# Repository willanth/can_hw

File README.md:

# can_hw
CANBus interface hardware PCB design

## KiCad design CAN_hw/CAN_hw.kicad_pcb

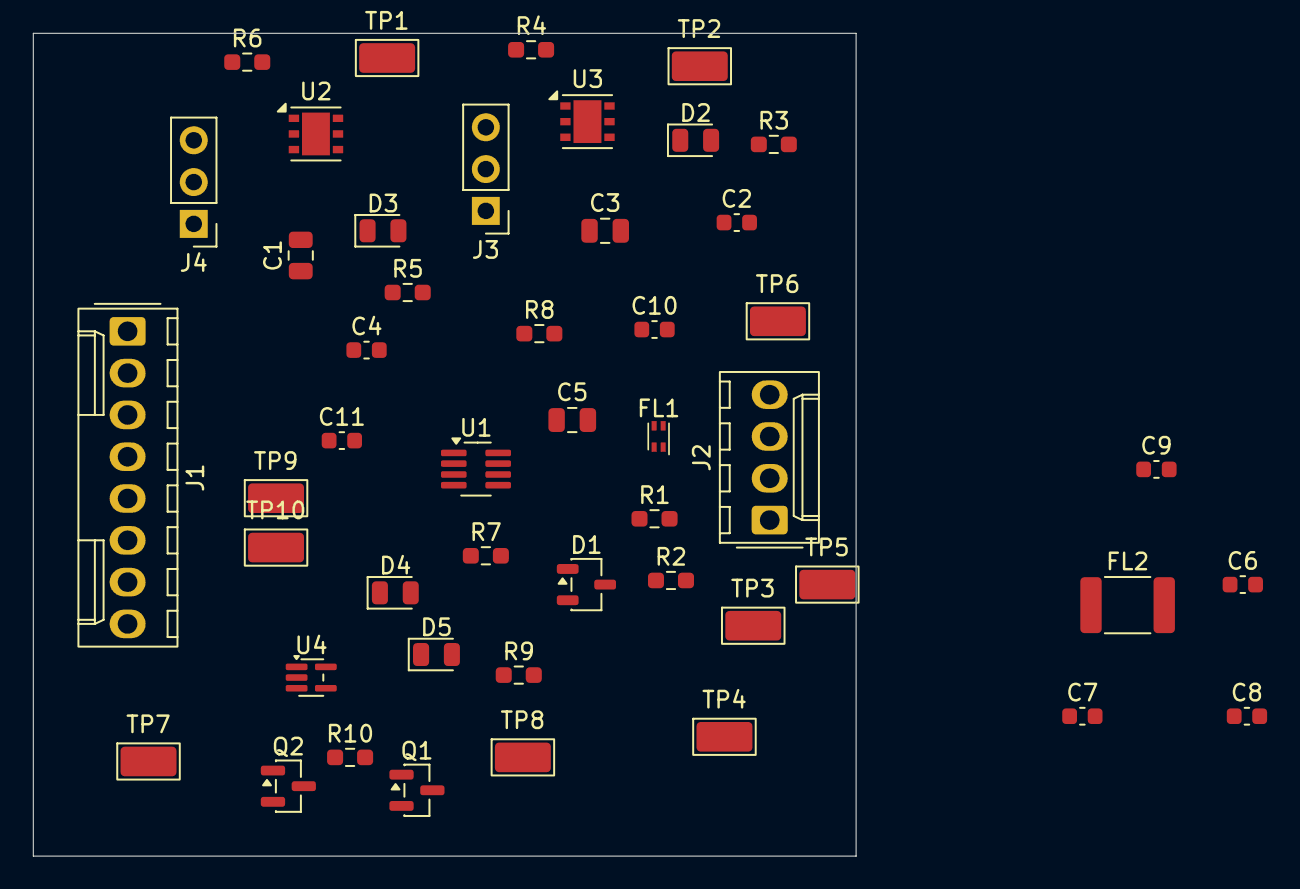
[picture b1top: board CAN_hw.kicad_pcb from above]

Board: 2 copper layers, 50.0 x 50.0 mm, 48 parts (0 on the bottom side), 26 nets, no tracks yet.

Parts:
C1: 4.7nF 50V; C_0805_2012Metric
C2, C4: 4.7uF 16V; C_0603_1608Metric
C3, C5: 4.7uF 50V; C_0805_2012Metric
C6, C7, C8, C9: 100pF; C_0603_1608Metric
C10, C11: 100nF; C_0603_1608Metric
D1: ESDA5V3L; SOT-23-3
D2, D3, D4, D5: LED; LED_0805_2012Metric
FL1: 0603USB-222; L_CommonModeChoke_Coilcraft_0603USB
FL2: ACT45-101; L_1812_4532Metric_Pad1.30x3.40mm_HandSolder
J1: Conn_01x08_Pin; Molex_KK-254_AE-6410-08A_1x08_P2.54mm_Vertical
J2: Conn_01x04_Pin; Molex_KK-254_AE-6410-04A_1x04_P2.54mm_Vertical
J3, J4: Conn_01x03_Pin; PinHeader_1x03_P2.54mm_Vertical
Q1, Q2: 2N7002; SOT-23
R1, R2: 60R; R_0603_1608Metric_Pad0.98x0.95mm_HandSolder
R3, R5, R9, R10: R; R_0603_1608Metric_Pad0.98x0.95mm_HandSolder
R4, R6, R7, R8: 10k; R_0603_1608Metric_Pad0.98x0.95mm_HandSolder
TP1, TP2, TP3, TP4, TP5, TP6, TP7, TP8, TP9, TP10: TestPoint_Alt; TestPoint_Keystone_5015_Micro_Mini
U1: TCAN337G; SOT-23-8_Handsoldering
U2: LDO40LPU50RY; DFN-6-1EP_3x3mm_P0.95mm_EP1.7x2.6mm
U3: LDO40LPU33RY; DFN-6-1EP_3x3mm_P0.95mm_EP1.7x2.6mm
U4: 74AHC1G04; SOT-353_SC-70-5

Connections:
+3.3V: C2.1, C10.1, C11.1, D2.2 (A), D4.2 (A), D5.2 (A), J1.3, R7.1, TP2.1, U1.3 (VCC), U3.4 (Vout), U3.5 (Vsense), U4.5 (VCC)
+5V: C4.1, D3.2 (A), J1.1, TP1.1, U2.4 (Vout), U2.5 (Vsense)
/CAN+: C9.2, D1.1 (K), J2.2, R1.1, TP3.1
/CAN-: C8.1, D1.2 (K), J2.3, R2.2, TP4.1
/FAULT: J1.7, R7.2, TP7.1, U1.5 (FAULT), U4.2
/SILENT: J1.8, Q1.1 (G), R8.1, TP8.1, U1.8 (S)
/V+: FL1.1, J2.1, TP5.1
/V-: FL1.4, J2.4, TP6.1
GND: C1.2, C2.2, C3.2, C4.2, C5.2, C6.2, C7.1, C8.2, C9.1, C10.2, C11.2, D1.3 (A), FL1.3, J1.2, J1.4, J3.3, J4.3, Q1.2 (S), Q2.2 (S), R3.2, R5.2, R8.2, U1.2 (GND), U2.1 (GND), U2.7 (GND), U3.1 (GND), U3.7 (GND), U4.3 (GND)
unnamed: C1.1, R1.2, R2.1
unnamed: D2.1 (K), R3.1
unnamed: D3.1 (K), R5.1
unnamed: D4.1 (K), R9.1
unnamed: D5.1 (K), R10.1
unnamed: J1.5, TP9.1, U1.1 (TXD)
unnamed: J1.6, TP10.1, U1.4 (RXD)
unnamed: J3.2, R4.2
unnamed: J4.2, R6.2
unnamed: Q1.3 (D), R9.2
unnamed: Q2.3 (D), R10.2
unnamed: Q2.1 (G), U4.4
unnamed: C7.2, FL2.1, U1.7 (CANH)
unnamed: C6.1, FL2.2, U1.6 (CANL)
unnamed: R6.1, U2.2 (EN)
unnamed: R4.1, U3.2 (EN)
VCC: C3.1, C5.1, FL1.2, J3.1, J4.1, U2.3 (Vin), U3.3 (Vin)

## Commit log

2026-01-31 initial schematic layout complete with footprints
2026-01-31 pcb layout begun, replacement of CAN common mode choke footprint required. PCB edge cuts need refinement, mounting holes req as well
